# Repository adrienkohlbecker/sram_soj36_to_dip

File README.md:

# sram_soj36_to_dip

This project converts an IS61C5128AL (SOJ-36) SRAM to an AS6C4008 (DIP-32) SRAM. It includes pinout conversion so the final pinout is the one of a AS6C4008 chip, allowing drop-in replacement with a faster chip (eg. 55ns to 10ns). Hand-soldering the chip is doable with a thin solder wire (I used 0.38mm solder wire for this). A spot for a 0.1uF decoupling capacitor is also provided.

## End result

## Schematic

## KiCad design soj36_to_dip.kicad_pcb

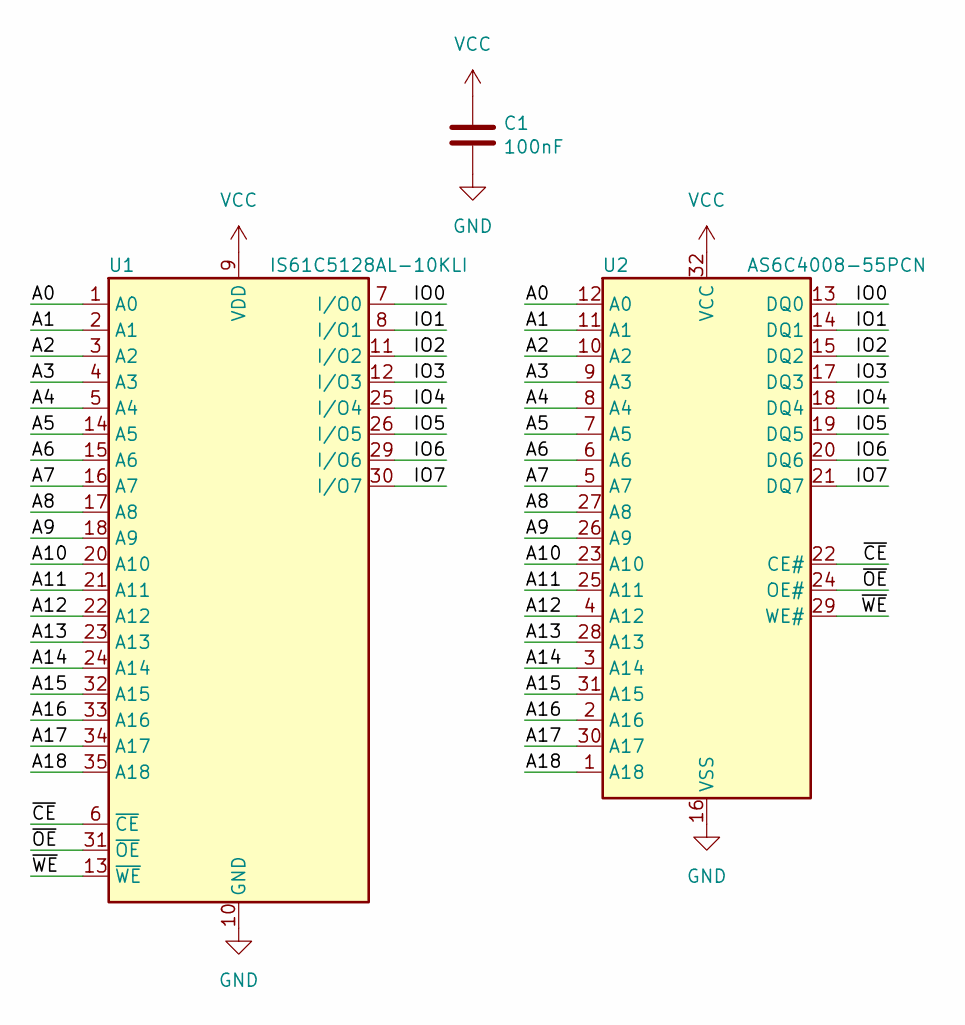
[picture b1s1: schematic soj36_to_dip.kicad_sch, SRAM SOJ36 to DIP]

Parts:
C1: 100nF; C_0805_2012Metric_Pad1.18x1.45mm_HandSolder
U1: IS61C5128AL-10KLI; SOJ-36_10.16x23.49mm_P1.27mm
U2: AS6C4008-55PCN; DIP-32_W15.24mm

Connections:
A0: U1.1 (A0), U2.12 (A0)
A1: U1.2 (A1), U2.11 (A1)
A2: U1.3 (A2), U2.10 (A2)
A3: U1.4 (A3), U2.9 (A3)
A4: U1.5 (A4), U2.8 (A4)
A5: U1.14 (A5), U2.7 (A5)
A6: U1.15 (A6), U2.6 (A6)
A7: U1.16 (A7), U2.5 (A7)
A8: U1.17 (A8), U2.27 (A8)
A9: U1.18 (A9), U2.26 (A9)
A10: U1.20 (A10), U2.23 (A10)
A11: U1.21 (A11), U2.25 (A11)
A12: U1.22 (A12), U2.4 (A12)
A13: U1.23 (A13), U2.28 (A13)
A14: U1.24 (A14), U2.3 (A14)
A15: U1.32 (A15), U2.31 (A15)
A16: U1.33 (A16), U2.2 (A16)
A17: U1.34 (A17), U2.30 (A17)
A18: U1.35 (A18), U2.1 (A18)
GND: C1.2, U1.10 (GND), U1.28 (GND), U2.16 (VSS)
IO0: U1.7 (I/O0), U2.13 (DQ0)
IO1: U1.8 (I/O1), U2.14 (DQ1)
IO2: U1.11 (I/O2), U2.15 (DQ2)
IO3: U1.12 (I/O3), U2.17 (DQ3)
IO4: U1.25 (I/O4), U2.18 (DQ4)
IO5: U1.26 (I/O5), U2.19 (DQ5)
IO6: U1.29 (I/O6), U2.20 (DQ6)
IO7: U1.30 (I/O7), U2.21 (DQ7)
VCC: C1.1, U1.9 (VDD), U1.27 (VDD), U2.32 (VCC)
~CE: U1.6 (~CE), U2.22 (CE#)
~OE: U1.31 (~OE), U2.24 (OE#)
~WE: U1.13 (~WE), U2.29 (WE#)

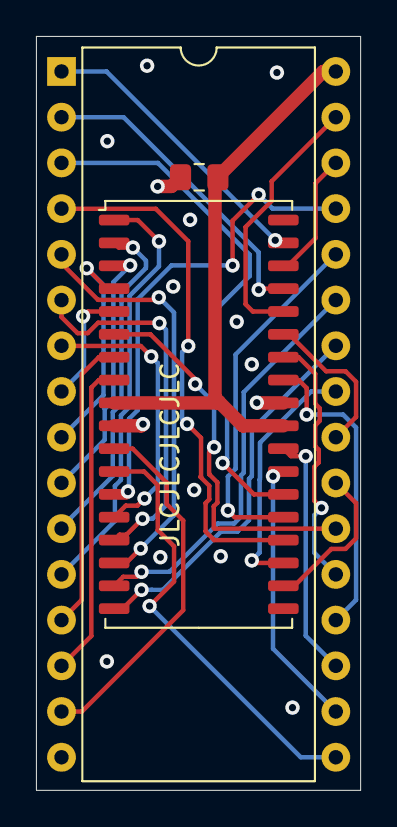
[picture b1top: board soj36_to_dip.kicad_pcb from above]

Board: 4 copper layers, 18.0 x 41.9 mm, 3 parts (0 on the bottom side), 32 nets.

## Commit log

2021-11-14 Publish project
2021-11-14 Add documentation
2023-06-06 Update for KiCad 6
